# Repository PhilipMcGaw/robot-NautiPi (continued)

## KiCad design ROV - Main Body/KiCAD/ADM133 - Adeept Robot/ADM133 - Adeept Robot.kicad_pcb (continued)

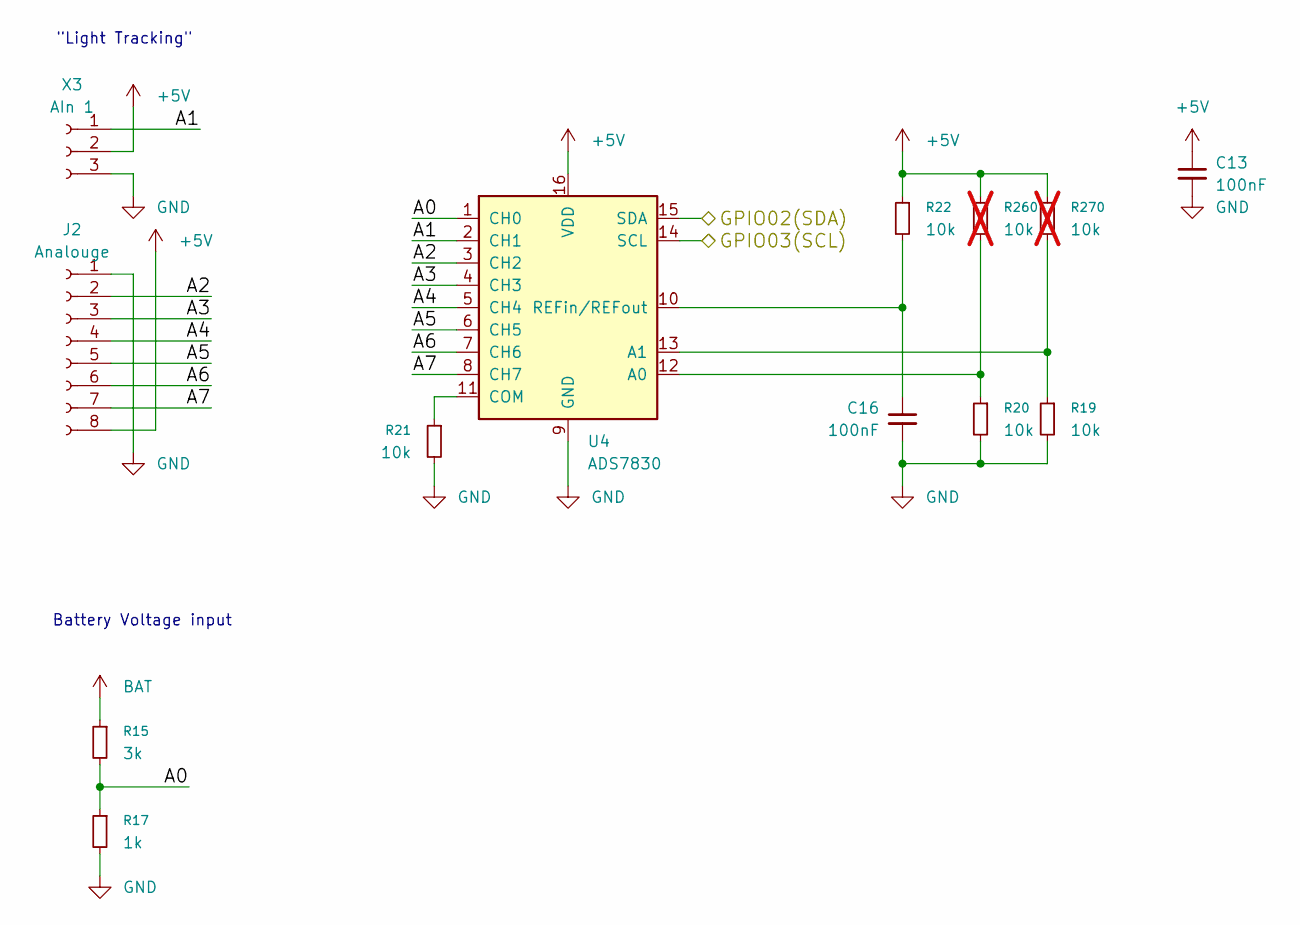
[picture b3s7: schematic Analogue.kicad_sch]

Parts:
C13, C16: 100nF; C_0805_2012Metric_Pad1.18x1.45mm_HandSolder
J2: Analouge; PinSocket_1x08_P2.54mm_Vertical
R15: 3k; R_0805_2012Metric_Pad1.20x1.40mm_HandSolder
R17: 1k; R_0805_2012Metric_Pad1.20x1.40mm_HandSolder
R19, R20, R21, R22: 10k; R_0805_2012Metric_Pad1.20x1.40mm_HandSolder
R260, R270: 10k; R_0805_2012Metric_Pad1.20x1.40mm_HandSolder; not fitted
U4: ADS7830; TSSOP-16_4.4x5mm_P0.65mm; Digikey 296-25899-1-ND
X3: AIn 1; JST_EH_B3B-EH-A_1x03_P2.50mm_Vertical

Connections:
/Analogue Interface/A0: R15.2, R17.1, U4.1 (CH0)
/Analogue Interface/A1: U4.2 (CH1), X3.1
/Analogue Interface/A2: J2.2, U4.3 (CH2)
/Analogue Interface/A3: J2.3, U4.4 (CH3)
/Analogue Interface/A4: J2.4, U4.5 (CH4)
/Analogue Interface/A5: J2.5, U4.6 (CH5)
/Analogue Interface/A6: J2.6, U4.7 (CH6)
/Analogue Interface/A7: J2.7, U4.8 (CH7)
/Analogue Interface/GPIO02(SDA): U4.15 (SDA); also elsewhere on the board
/Analogue Interface/GPIO03(SCL): U4.14 (SCL); also elsewhere on the board
BAT: R15.1; also elsewhere on the board
unnamed: R20.1, R260.2, U4.12 (A0)
unnamed: R19.1, R270.2, U4.13 (A1)
unnamed: R21.1, U4.11 (COM)

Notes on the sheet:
"Light Tracking"
Battery Voltage input

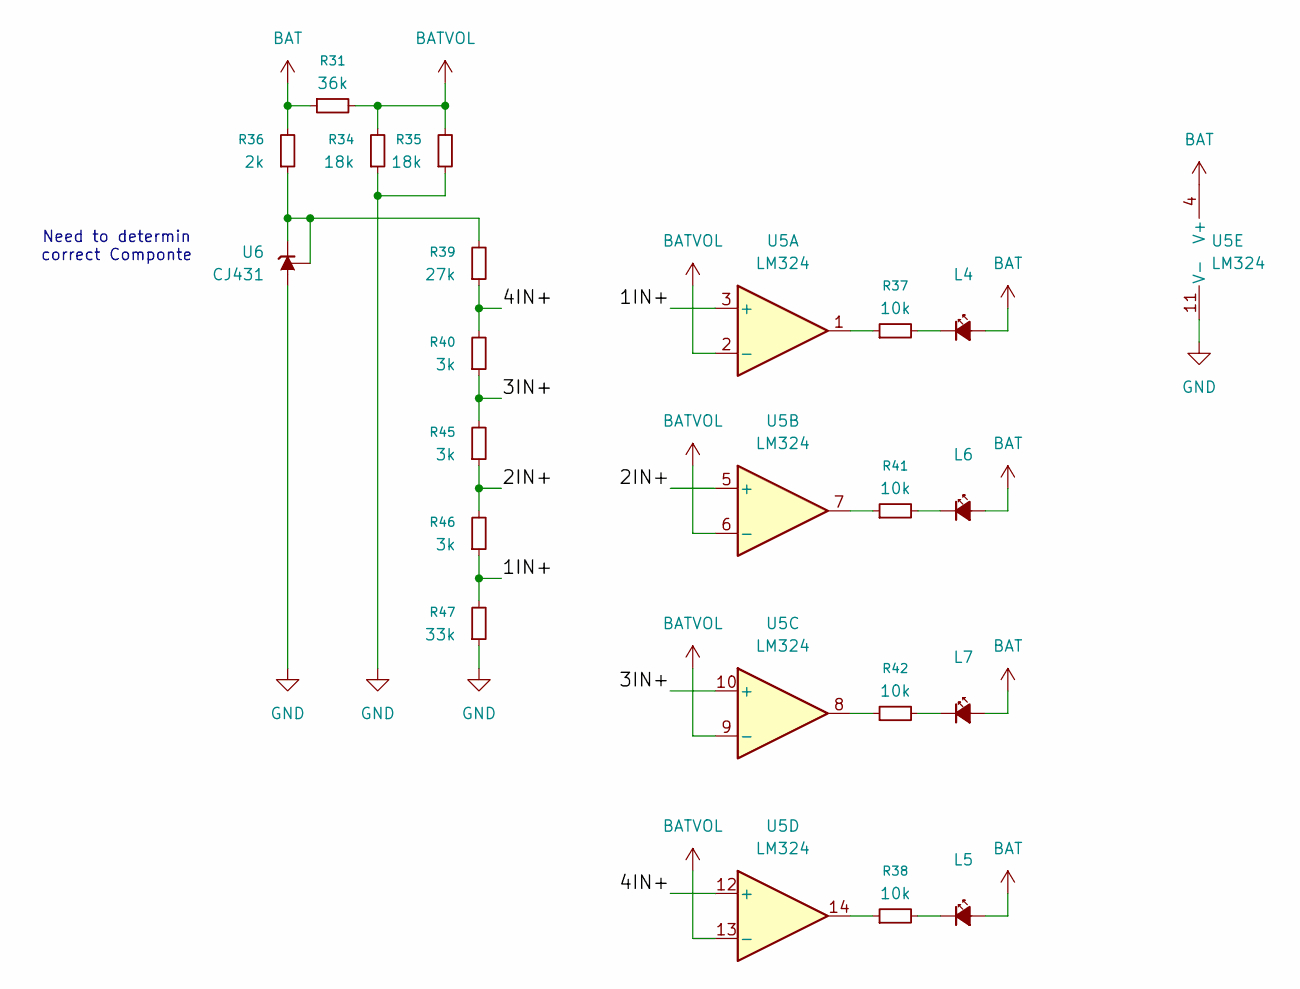
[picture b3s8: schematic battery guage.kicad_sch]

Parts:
L4, L5, L6, L7: LED_0805_2012Metric_Pad1.15x1.40mm_HandSolder
R31: 36k; R_0805_2012Metric_Pad1.20x1.40mm_HandSolder
R34, R35: 18k; R_0805_2012Metric_Pad1.20x1.40mm_HandSolder
R36: 2k; R_0805_2012Metric_Pad1.20x1.40mm_HandSolder
R37, R38, R41, R42: 10k; R_0805_2012Metric_Pad1.20x1.40mm_HandSolder
R39: 27k; R_0805_2012Metric_Pad1.20x1.40mm_HandSolder
R40, R45, R46: 3k; R_0805_2012Metric_Pad1.20x1.40mm_HandSolder
R47: 33k; R_0805_2012Metric_Pad1.20x1.40mm_HandSolder
U5: LM324; TSSOP-14_4.4x5mm_P0.65mm
U6: CJ431; SOT-23_Handsoldering

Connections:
/Battery Guage/1IN+: R46.1, R47.2, U5.3 (+)
/Battery Guage/2IN+: R45.1, R46.2, U5.5 (+)
/Battery Guage/3IN+: R40.1, R45.2, U5.10 (+)
/Battery Guage/4IN+: R39.1, R40.2, U5.12 (+)
BAT: L4.2 (A), L5.2 (A), L6.2 (A), L7.2 (A), R31.1, R36.2, U5.4 (V+); also elsewhere on the board
BATVOL: R31.2, R34.2, R35.2, U5.2 (-), U5.6 (-), U5.9 (-), U5.13 (-)
unnamed: L4.1 (K), R37.2
unnamed: L5.1 (K), R38.2
unnamed: L6.1 (K), R41.2
unnamed: L7.1 (K), R42.2
unnamed: R37.1, U5.1
unnamed: R38.1, U5.14
unnamed: R41.1, U5.7
unnamed: R42.1, U5.8
unnamed: R36.1, R39.2, U6.1 (REF), U6.2 (K)

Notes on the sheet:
Need to determin correct Componte

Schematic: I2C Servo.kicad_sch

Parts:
C4: 100nF; C_0805_2012Metric_Pad1.18x1.45mm_HandSolder
CH0, CH1, CH2, CH3, CH4, CH5, CH6, CH7, CH8, CH9, CH10, CH11, CH12, CH13, CH14, CH15: Servo; PinHeader_1x03_P2.54mm_Vertical
R2, R3, R4, R5, R6, R51: 10k; R_0805_2012Metric_Pad1.20x1.40mm_HandSolder; not fitted
R9, R10, R11, R12, R13, R49: 10k; R_0805_2012Metric_Pad1.20x1.40mm_HandSolder
U2: PCA9685PW; TSSOP-28_4.4x9.7mm_P0.65mm

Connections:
/Analogue Interface/GPIO02(SDA): U2.27 (SDA); also elsewhere on the board
/Analogue Interface/GPIO03(SCL): U2.26 (SCL); also elsewhere on the board
/Servo Interface/CH0: CH0.1, U2.6 (LED0)
/Servo Interface/CH1: CH1.1, U2.7 (LED1)
/Servo Interface/CH2: CH2.1, U2.8 (LED2)
/Servo Interface/CH3: CH3.1, U2.9 (LED3)
/Servo Interface/CH4: CH4.1, U2.10 (LED4)
/Servo Interface/CH5: CH5.1, U2.11 (LED5)
/Servo Interface/CH6: CH6.1, U2.12 (LED6)
/Servo Interface/CH7: CH7.1, U2.13 (LED7)
/Servo Interface/CH8: CH8.1, U2.15 (LED8); also elsewhere on the board
/Servo Interface/CH9: CH9.1, U2.16 (LED9); also elsewhere on the board
/Servo Interface/CH10: CH10.1, U2.17 (LED10); also elsewhere on the board
/Servo Interface/CH11: CH11.1, U2.18 (LED11); also elsewhere on the board
/Servo Interface/CH12: CH12.1, U2.19 (LED12); also elsewhere on the board
/Servo Interface/CH13: CH13.1, U2.20 (LED13); also elsewhere on the board
/Servo Interface/CH14: CH14.1, U2.21 (LED14); also elsewhere on the board
/Servo Interface/CH15: CH15.1, U2.22 (LED15); also elsewhere on the board
unnamed: R6.2, R9.1, U2.1 (A0)
unnamed: R5.2, R10.1, U2.2 (A1)
unnamed: R4.2, R11.1, U2.3 (A2)
unnamed: R3.2, R12.1, U2.4 (A3)
unnamed: R2.2, R13.1, U2.5 (A4)
unnamed: R49.1, R51.2, U2.24 (A5)

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
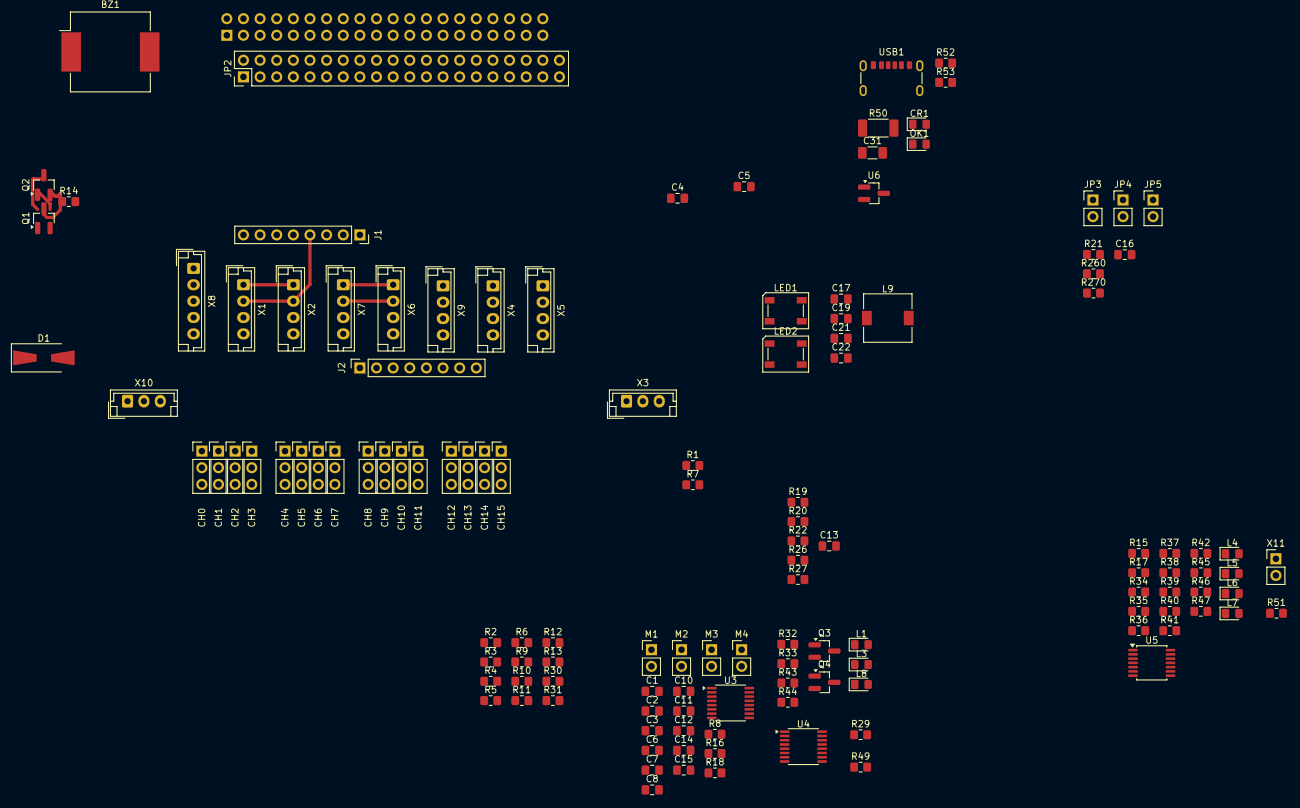
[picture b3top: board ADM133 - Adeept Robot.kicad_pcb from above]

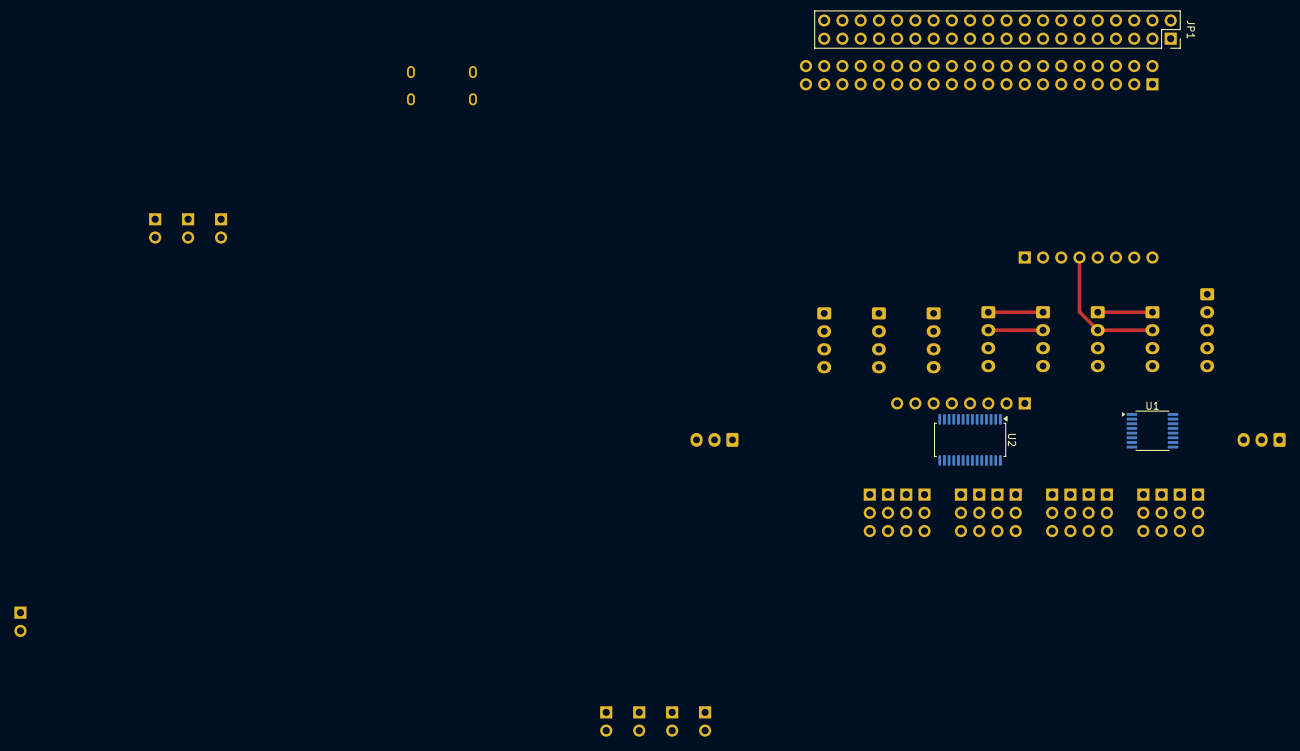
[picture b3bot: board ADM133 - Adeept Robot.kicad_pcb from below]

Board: 2 copper layers, 133 parts (3 on the bottom side), 113 nets.

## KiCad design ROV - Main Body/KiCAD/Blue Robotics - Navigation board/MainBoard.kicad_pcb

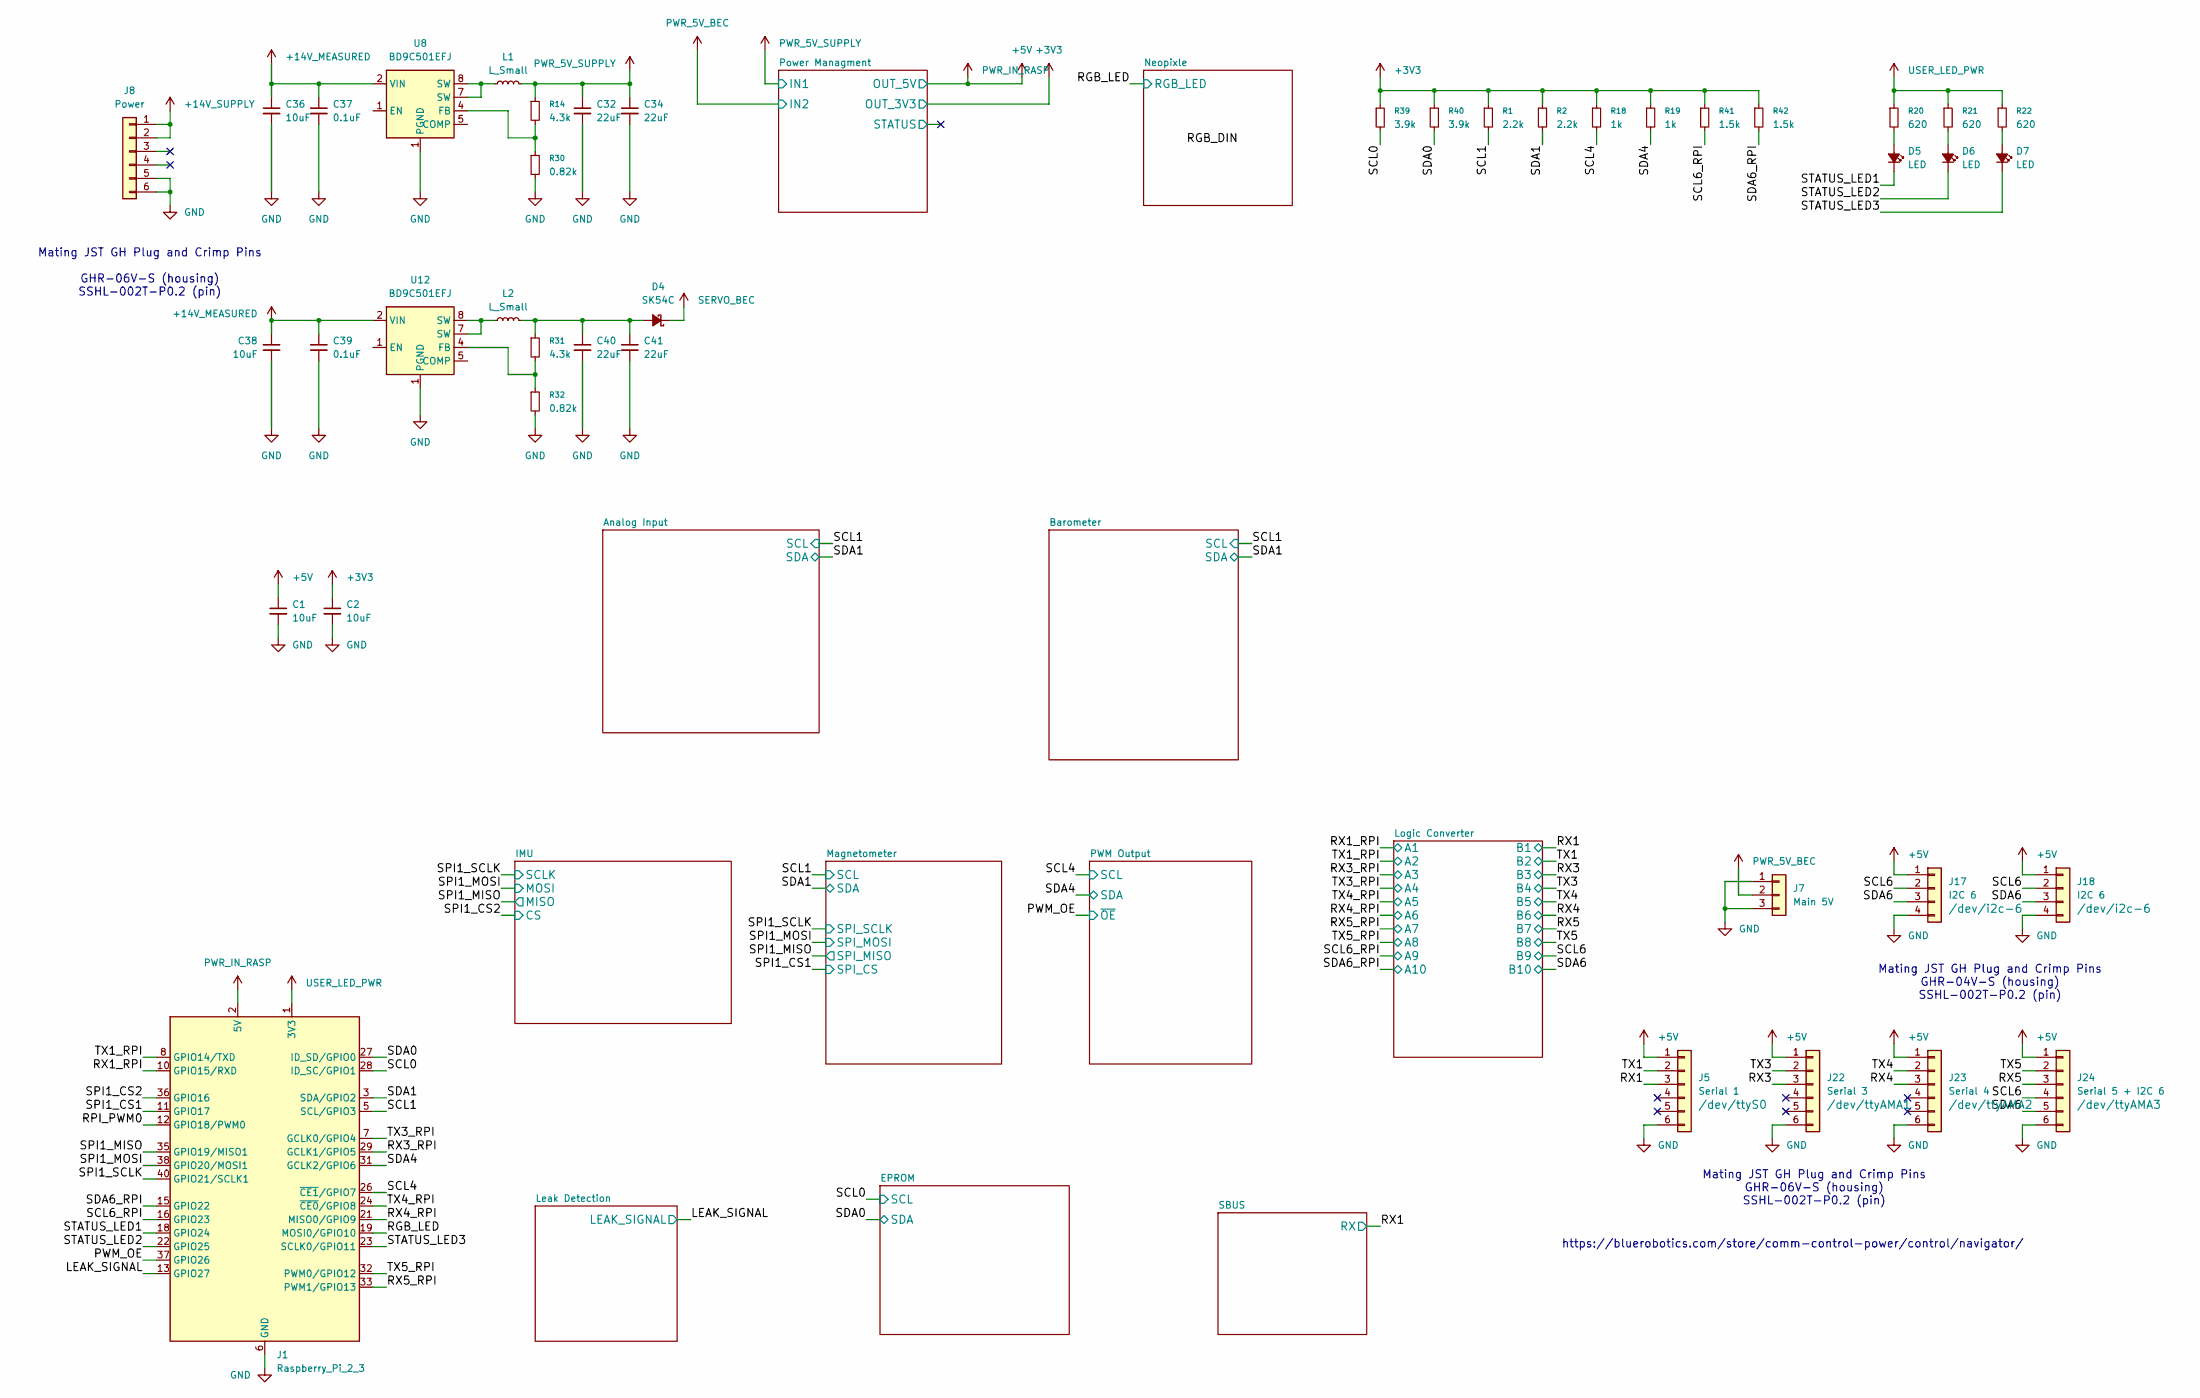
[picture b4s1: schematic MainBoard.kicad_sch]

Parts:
C1, C2, C36, C38: 10uF; C_0805_2012Metric_Pad1.18x1.45mm_HandSolder
C32, C34, C40, C41: 22uF; C_0805_2012Metric_Pad1.18x1.45mm_HandSolder
C37, C39: 0.1uF; C_0805_2012Metric_Pad1.18x1.45mm_HandSolder
D4: SK54C; D_SMC_Handsoldering; Farnell 3519515
D5, D6, D7: LED; LED_0805_2012Metric_Pad1.15x1.40mm_HandSolder; DigiKey 160-1426-1-ND
J1: Raspberry_Pi_2_3; PinSocket_2x20_P2.54mm_Vertical
J5: Serial 1; JST_GH_BM06B-GHS-TBT_1x06-1MP_P1.25mm_Vertical
J7: Main 5V; PinHeader_1x03_P2.54mm_Vertical
J8: Power; JST_GH_BM06B-GHS-TBT_1x06-1MP_P1.25mm_Vertical
J17, J18: I2C 6; JST_GH_BM04B-GHS-TBT_1x04-1MP_P1.25mm_Vertical
J22: Serial 3; JST_GH_BM06B-GHS-TBT_1x06-1MP_P1.25mm_Vertical
J23: Serial 4; JST_GH_BM06B-GHS-TBT_1x06-1MP_P1.25mm_Vertical
J24: Serial 5 + I2C 6; JST_GH_BM06B-GHS-TBT_1x06-1MP_P1.25mm_Vertical
L1, L2: L_Small
R1, R2: 2.2k; R_0805_2012Metric_Pad1.20x1.40mm_HandSolder
R14, R31: 4.3k; R_0805_2012Metric_Pad1.20x1.40mm_HandSolder
R18, R19: 1k; R_0805_2012Metric_Pad1.20x1.40mm_HandSolder
R20, R21, R22: 620; R_0805_2012Metric_Pad1.20x1.40mm_HandSolder
R30, R32: 0.82k; R_0805_2012Metric_Pad1.20x1.40mm_HandSolder
R39, R40: 3.9k; R_0805_2012Metric_Pad1.20x1.40mm_HandSolder
R41, R42: 1.5k; R_0805_2012Metric_Pad1.20x1.40mm_HandSolder
U8, U12: BD9C501EFJ; HTSOP-8-1EP_3.9x4.9mm_P1.27mm_EP2.4x3.2mm_ThermalVias

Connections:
+3V3: C2.1, R1.1, R2.1, R18.1, R19.1, R39.1, R40.1, R41.1, R42.1; also elsewhere on the board
+5V: C1.1, J1.2 (5V), J1.4 (5V), J5.1, J17.1, J18.1, J22.1, J23.1, J24.1; also elsewhere on the board
+14V_MEASURED: C36.1, C37.1, C38.1, C39.1, U8.2 (VIN), U12.2 (VIN); also elsewhere on the board
+14V_SUPPLY: J8.1, J8.2; also elsewhere on the board
/LEAK_SIGNAL: J1.13 (GPIO27); also elsewhere on the board
/PWM_OE: J1.37 (GPIO26); also elsewhere on the board
/RGB_LED: J1.19 (MOSI0/GPIO10); also elsewhere on the board
/RPI_PWM0: J1.12 (GPIO18/PWM0)
/RX1: J5.3; also elsewhere on the board
/RX1_RPI: J1.10 (GPIO15/RXD); also elsewhere on the board
/RX3: J22.3; also elsewhere on the board
/RX3_RPI: J1.29 (GCLK1/GPIO5); also elsewhere on the board
/RX4: J23.3; also elsewhere on the board
/RX4_RPI: J1.21 (MISO0/GPIO9); also elsewhere on the board
/RX5: J24.3; also elsewhere on the board
/RX5_RPI: J1.33 (PWM1/GPIO13); also elsewhere on the board
/SCL0: J1.28 (ID_SC/GPIO1), R39.2
/SCL1: J1.5 (SCL/GPIO3), R1.2; also elsewhere on the board
/SCL4: J1.26 (~CE1/GPIO7), R18.2; also elsewhere on the board
/SCL6: J17.2, J18.2, J24.4; also elsewhere on the board
/SCL6_RPI: J1.16 (GPIO23), R41.2; also elsewhere on the board
/SDA0: J1.27 (ID_SD/GPIO0), R40.2
/SDA1: J1.3 (SDA/GPIO2), R2.2; also elsewhere on the board
/SDA4: J1.31 (GCLK2/GPIO6), R19.2; also elsewhere on the board
/SDA6: J17.3, J18.3, J24.5; also elsewhere on the board
/SDA6_RPI: J1.15 (GPIO22), R42.2; also elsewhere on the board
/SPI1_CS1: J1.11 (GPIO17)
/SPI1_CS2: J1.36 (GPIO16); also elsewhere on the board
/SPI1_MISO: J1.35 (GPIO19/MISO1); also elsewhere on the board
/SPI1_MOSI: J1.38 (GPIO20/MOSI1); also elsewhere on the board
/SPI1_SCLK: J1.40 (GPIO21/SCLK1); also elsewhere on the board
/STATUS_LED1: D5.1 (K), J1.18 (GPIO24)
/STATUS_LED2: D6.1 (K), J1.22 (GPIO25)
/STATUS_LED3: D7.1 (K), J1.23 (SCLK0/GPIO11)
/TX1: J5.2; also elsewhere on the board
/TX1_RPI: J1.8 (GPIO14/TXD); also elsewhere on the board
/TX3: J22.2; also elsewhere on the board
/TX3_RPI: J1.7 (GCLK0/GPIO4); also elsewhere on the board
/TX4: J23.2; also elsewhere on the board
/TX4_RPI: J1.24 (~CE0/GPIO8); also elsewhere on the board
/TX5: J24.2; also elsewhere on the board
/TX5_RPI: J1.32 (PWM0/GPIO12); also elsewhere on the board
GND: C1.2, C2.2, C32.2, C34.2, C36.2, C37.2, C38.2, C39.2, C40.2, C41.2, J1.6 (GND), J1.9 (GND), J1.14 (GND), J1.20 (GND), J1.25 (GND), J1.30 (GND), J1.34 (GND), J1.39 (GND), J5.6, J7.1, J7.3, J8.5, J8.6, J17.4, J18.4, J22.6, J23.6, J24.6, R30.2, R32.2, U8.1 (PGND), U8.3 (AGND), U8.9 (AGND), U12.1 (PGND), U12.3 (AGND), U12.9 (AGND); also elsewhere on the board
unnamed: C40.1, C41.1, D4.2 (A), L2.2, R31.1
unnamed: D5.2 (A), R20.2
unnamed: D6.2 (A), R21.2
unnamed: D7.2 (A), R22.2
unnamed: L1.1, U8.7 (SW), U8.8 (SW)
unnamed: L2.1, U12.7 (SW), U12.8 (SW)
unnamed: R14.2, R30.1, U8.4 (FB)
unnamed: R31.2, R32.1, U12.4 (FB)
PWR_5V_BEC: J7.2; also elsewhere on the board
PWR_5V_SUPPLY: C32.1, C34.1, L1.2, R14.1; also elsewhere on the board
SERVO_BEC: D4.1 (K); also elsewhere on the board
USER_LED_PWR: J1.1 (3V3), J1.17 (3V3), R20.1, R21.1, R22.1

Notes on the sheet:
Mating JST GH Plug and Crimp Pins GHR-06V-S (housing) SSHL-002T-P0.2 (pin)
Mating JST GH Plug and Crimp Pins GHR-06V-S (housing) SSHL-002T-P0.2 (pin)
Mating JST GH Plug and Crimp Pins GHR-04V-S (housing) SSHL-002T-P0.2 (pin)
https://bluerobotics.com/store/comm-control-power/control/navigator/

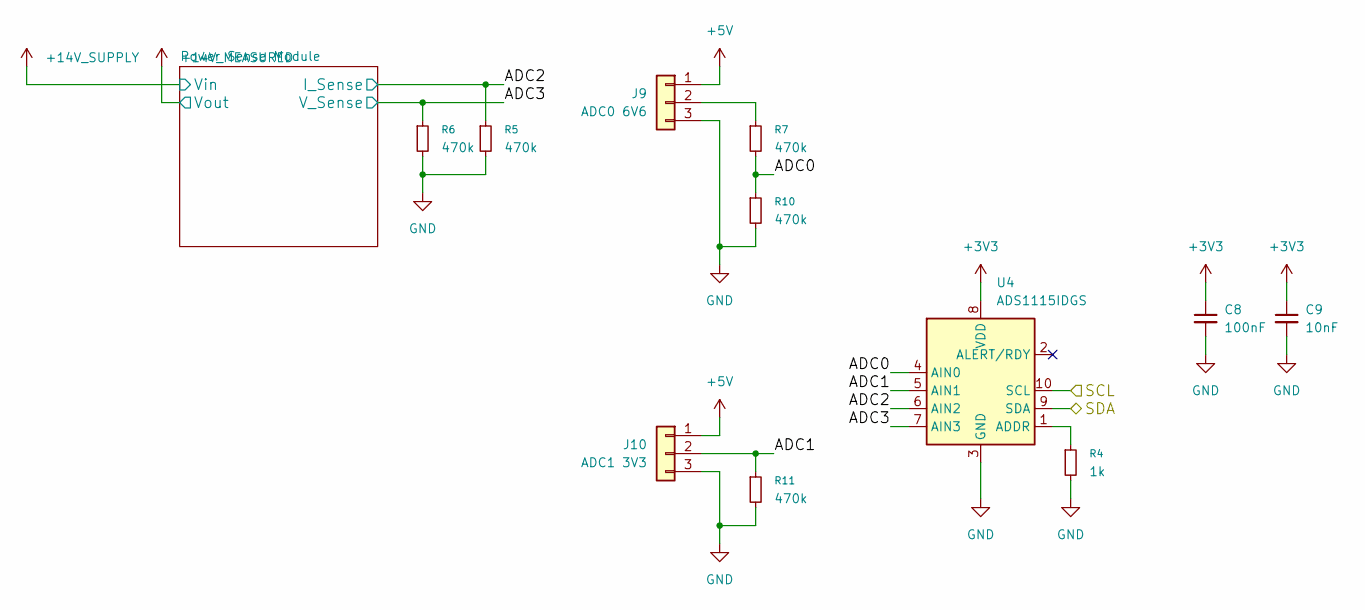
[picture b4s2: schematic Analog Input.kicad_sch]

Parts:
C8: 100nF; C_0805_2012Metric_Pad1.18x1.45mm_HandSolder
C9: 10nF; C_0805_2012Metric_Pad1.18x1.45mm_HandSolder
J9: ADC0 6V6; JST_GH_BM03B-GHS-TBT_1x03-1MP_P1.25mm_Vertical
J10: ADC1 3V3; JST_GH_BM03B-GHS-TBT_1x03-1MP_P1.25mm_Vertical
R4: 1k; R_0805_2012Metric_Pad1.20x1.40mm_HandSolder
R5, R6, R7, R10, R11: 470k; R_0805_2012Metric_Pad1.20x1.40mm_HandSolder
U4: ADS1115IDGS; TSSOP-10_3x3mm_P0.5mm

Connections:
+3V3: C8.1, C9.1, U4.8 (VDD); also elsewhere on the board
+5V: J9.1, J10.1; also elsewhere on the board
/Analog Input/ADC0: R7.2, R10.1, U4.4 (AIN0)
/Analog Input/ADC1: J10.2, R11.1, U4.5 (AIN1)
/Analog Input/ADC2: R5.1, U4.6 (AIN2); also elsewhere on the board
/Analog Input/ADC3: R6.1, U4.7 (AIN3); also elsewhere on the board
/SCL1: U4.10 (SCL); also elsewhere on the board
/SDA1: U4.9 (SDA); also elsewhere on the board
GND: C8.2, C9.2, J9.3, J10.3, R4.2, R5.2, R6.2, R10.2, R11.2, U4.3 (GND); also elsewhere on the board
unnamed: J9.2, R7.1
unnamed: R4.1, U4.1 (ADDR)

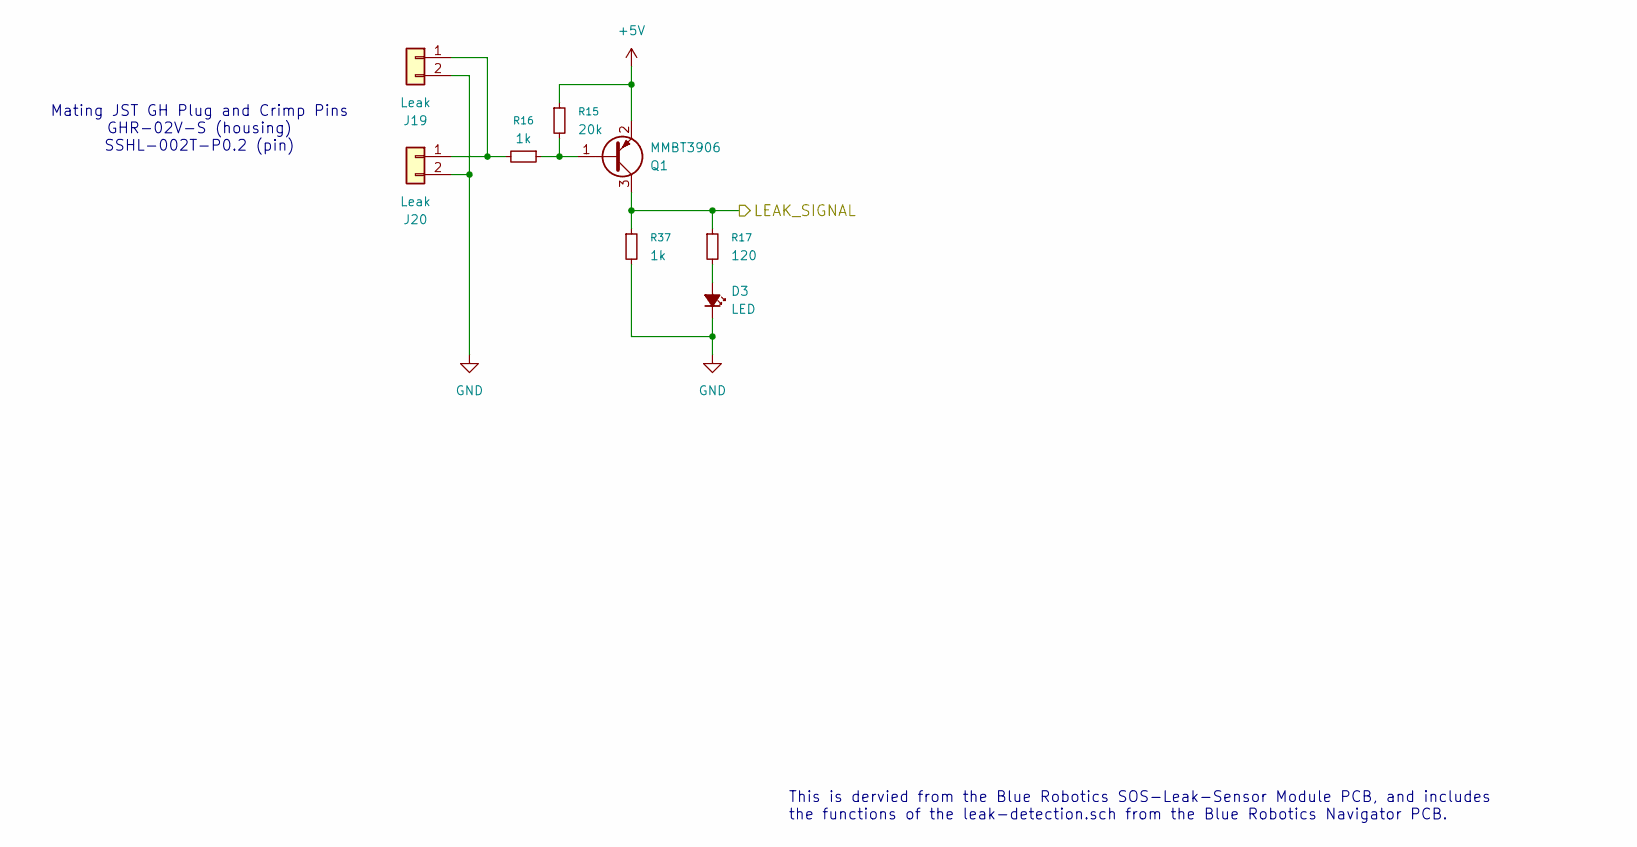
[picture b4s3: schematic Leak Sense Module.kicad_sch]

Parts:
D3: LED; LED_0805_2012Metric_Pad1.15x1.40mm_HandSolder; DigiKey 160-1426-1-ND
J19, J20: Leak; JST_GH_BM02B-GHS-TBT_1x02-1MP_P1.25mm_Vertical
Q1: MMBT3906; SOT-23
R15: 20k; R_0805_2012Metric_Pad1.20x1.40mm_HandSolder
R16, R37: 1k; R_0805_2012Metric_Pad1.20x1.40mm_HandSolder
R17: 120; R_0805_2012Metric_Pad1.20x1.40mm_HandSolder

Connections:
+5V: Q1.2 (E), R15.1; also elsewhere on the board
/LEAK_SIGNAL: Q1.3 (C), R17.1, R37.1; also elsewhere on the board
GND: D3.1 (K), J19.2, J20.2, R37.2; also elsewhere on the board
unnamed: D3.2 (A), R17.2
unnamed: J19.1, J20.1, R16.2
unnamed: Q1.1 (B), R15.2, R16.1

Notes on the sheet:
This is dervied from the Blue Robotics SOS-Leak-Sensor Module PCB, and includes the functions of the leak-detection.sch from the Blue Robotics Navigator PCB.
Mating JST GH Plug and Crimp Pins GHR-02V-S (housing) SSHL-002T-P0.2 (pin)

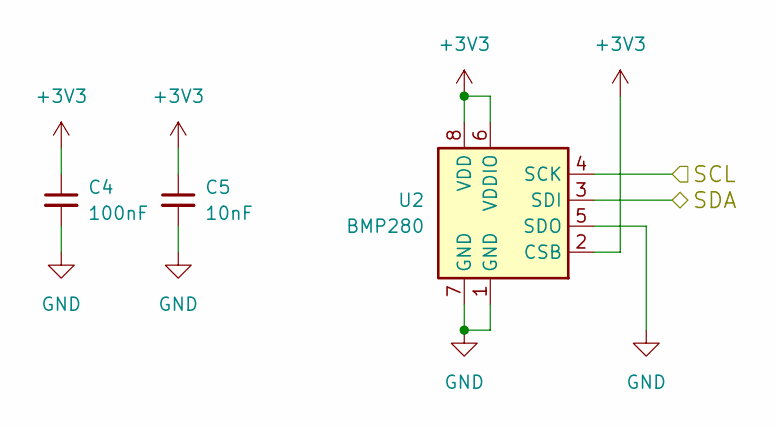
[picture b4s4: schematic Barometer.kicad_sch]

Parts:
C4: 100nF; C_0805_2012Metric_Pad1.18x1.45mm_HandSolder
C5: 10nF; C_0805_2012Metric_Pad1.18x1.45mm_HandSolder
U2: BMP280; Bosch_LGA-8_2x2.5mm_P0.65mm_ClockwisePinNumbering

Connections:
+3V3: C4.1, C5.1, U2.2 (CSB), U2.6 (VDDIO), U2.8 (VDD); also elsewhere on the board
/SCL1: U2.4 (SCK); also elsewhere on the board
/SDA1: U2.3 (SDI); also elsewhere on the board
GND: C4.2, C5.2, U2.1 (GND), U2.5 (SDO), U2.7 (GND); also elsewhere on the board

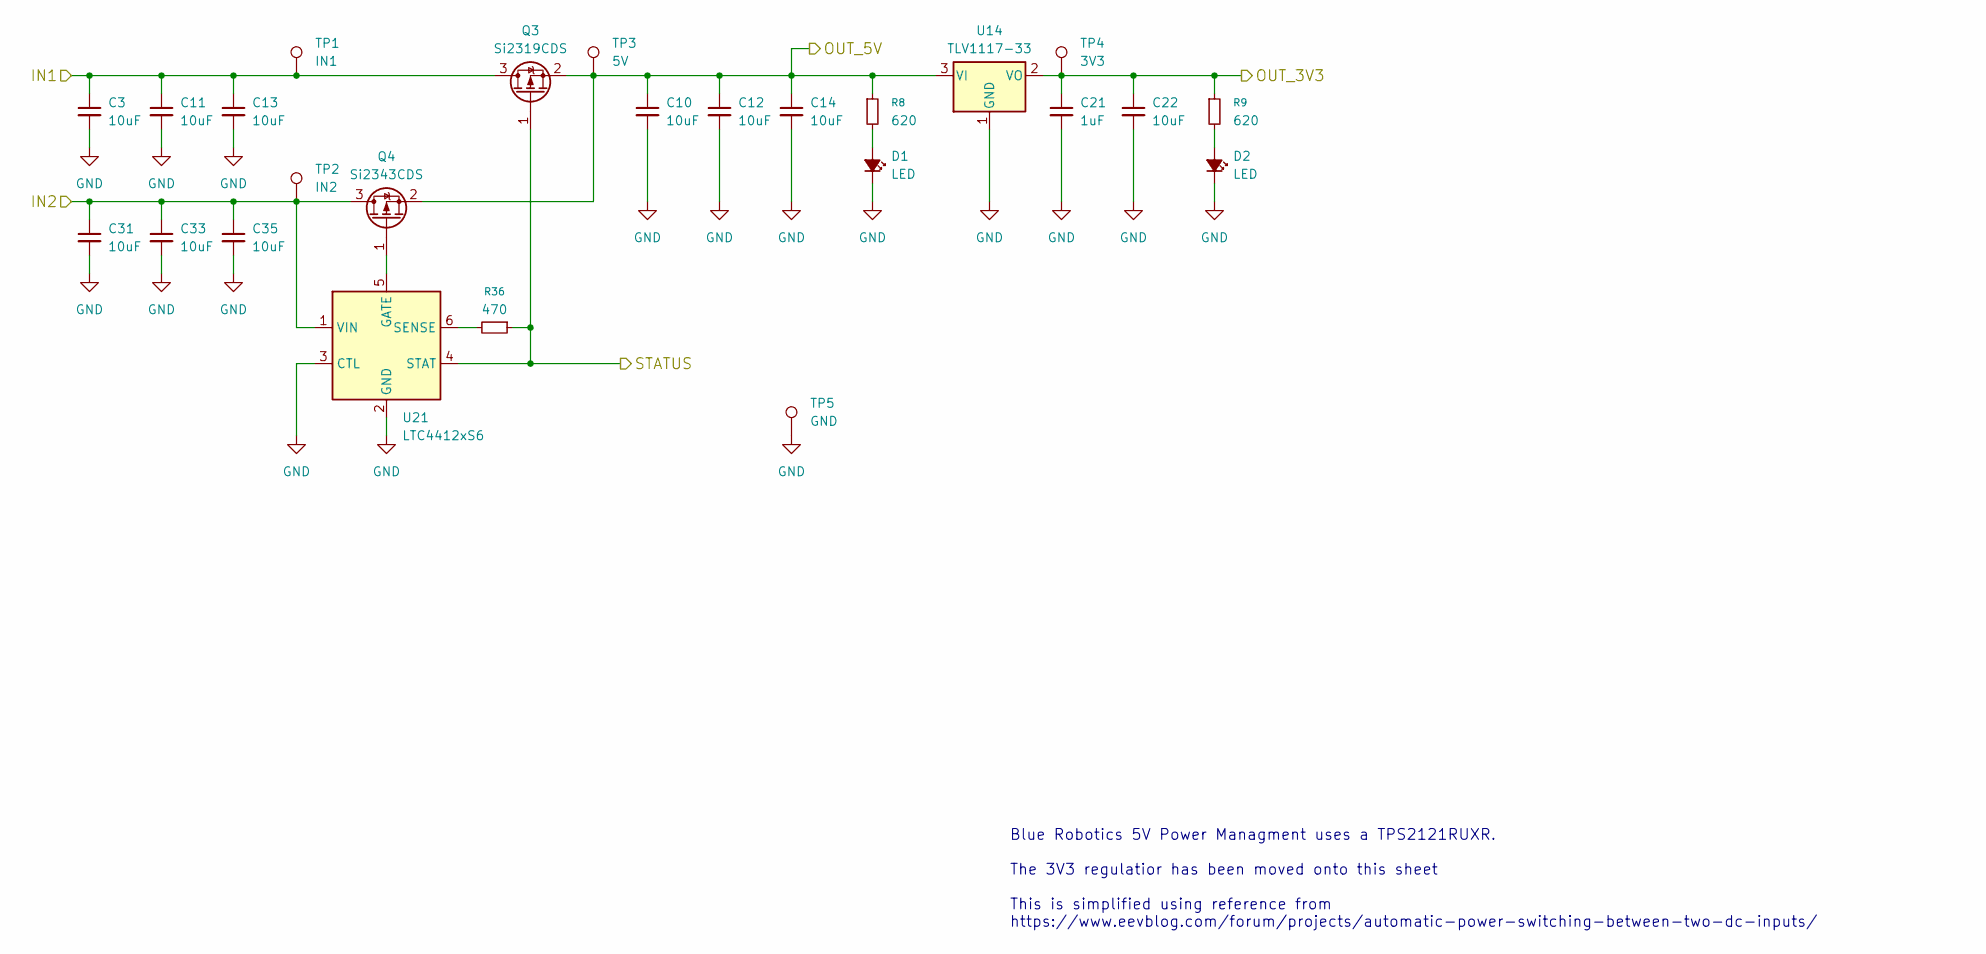
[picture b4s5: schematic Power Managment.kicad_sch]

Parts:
C3, C10, C11, C12, C13, C14, C22, C31, C33, C35: 10uF; C_0805_2012Metric_Pad1.18x1.45mm_HandSolder
C21: 1uF; C_0805_2012Metric_Pad1.18x1.45mm_HandSolder
D1, D2: LED; LED_0805_2012Metric_Pad1.15x1.40mm_HandSolder; DigiKey 160-1426-1-ND
Q3: Si2319CDS; SOT-23
Q4: Si2343CDS; SOT-23; Farnell 2335290
R8, R9: 620; R_0805_2012Metric_Pad1.20x1.40mm_HandSolder
R36: 470; R_0805_2012Metric_Pad1.20x1.40mm_HandSolder
TP1: IN1; TestPoint_Pad_D1.0mm
TP2: IN2; TestPoint_Pad_D1.0mm
TP3: 5V; TestPoint_Pad_D1.0mm
TP4: 3V3; TestPoint_Pad_D1.0mm
TP5: GND; TestPoint_Pad_D1.0mm
U14: TLV1117-33; SOT-223-3_TabPin2; Farnell 3007751
U21: LTC4412xS6; TSOT-23-6; Farnell 4025614

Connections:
+3V3: C21.1, C22.1, R9.1, TP4.1, U14.2 (VO); also elsewhere on the board
+5V: C10.1, C12.1, C14.1, Q3.2 (S), Q4.2 (S), R8.1, TP3.1, U14.3 (VI); also elsewhere on the board
/Power Managment/STATUS: Q3.1 (G), R36.1, U21.4 (STAT)
GND: C3.2, C10.2, C11.2, C12.2, C13.2, C14.2, C21.2, C22.2, C31.2, C33.2, C35.2, D1.1 (K), D2.1 (K), TP5.1, U14.1 (GND), U21.2 (GND), U21.3 (CTL); also elsewhere on the board
unnamed: D1.2 (A), R8.2
unnamed: D2.2 (A), R9.2
unnamed: Q4.1 (G), U21.5 (GATE)
unnamed: R36.2, U21.6 (SENSE)
PWR_5V_BEC: C31.1, C33.1, C35.1, Q4.3 (D), TP2.1, U21.1 (VIN); also elsewhere on the board
PWR_5V_SUPPLY: C3.1, C11.1, C13.1, Q3.3 (D), TP1.1; also elsewhere on the board

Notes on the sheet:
Blue Robotics 5V Power Managment uses a TPS2121RUXR. The 3V3 regulatior has been moved onto this sheet This is simplified using reference from https://www.eevblog.com/forum/projects/automatic-power-switching-between-two-dc-inputs/

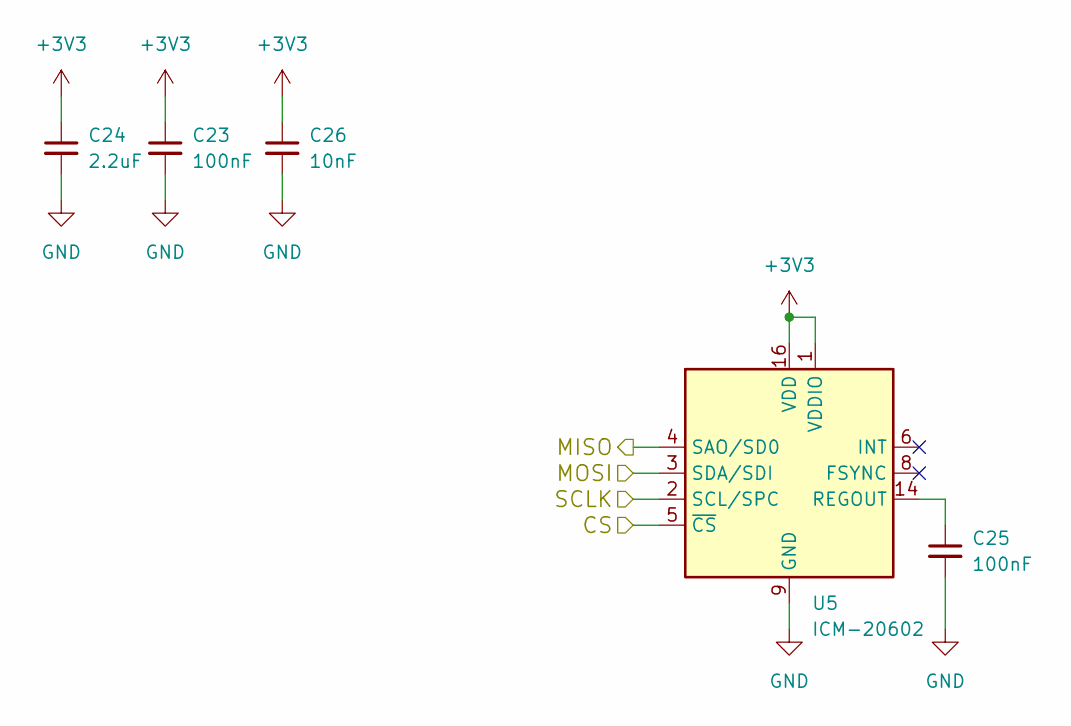
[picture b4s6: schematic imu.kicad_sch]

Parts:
C23, C25: 100nF; C_0805_2012Metric_Pad1.18x1.45mm_HandSolder
C24: 2.2uF; C_0805_2012Metric_Pad1.18x1.45mm_HandSolder
C26: 10nF; C_0805_2012Metric_Pad1.18x1.45mm_HandSolder
U5: ICM-20602; LGA-16_3x3mm_P0.5mm_LayoutBorder3x5y

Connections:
+3V3: C23.1, C24.1, C26.1, U5.1 (VDDIO), U5.16 (VDD); also elsewhere on the board
/SPI1_CS2: U5.5 (~CS); also elsewhere on the board
/SPI1_MISO: U5.4 (SAO/SD0); also elsewhere on the board
/SPI1_MOSI: U5.3 (SDA/SDI); also elsewhere on the board
/SPI1_SCLK: U5.2 (SCL/SPC); also elsewhere on the board
GND: C23.2, C24.2, C25.2, C26.2, U5.9 (GND), U5.10 (GND), U5.11 (GND), U5.12 (GND), U5.13 (GND), U5.15 (GND); also elsewhere on the board
unnamed: C25.1, U5.14 (REGOUT)
